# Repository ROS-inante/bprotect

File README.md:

# BProtect

This repository contains the design files and firmware for the BProtect battery management board.

## Overview
The battery management system consists of a LTC4281 Hot-Swap controller handling the power path control as well as a Espressif ESP32 running the interfacing firmware. 

The design was created in KiCad and can be found in the [board](/board) folder.
Some notes about design considerations, component selection and sizing are contained in the schematic.

The ESP32 runs the awesome [Tasmota](https://tasmota.github.io/docs/) firmware and has a custom driver for the LTC4281 written in [Berry](https://berry-lang.github.io/). It can be found in the [app](/app) folder.

## Usage
Assemble the board as per schematics and flash Tasmota (version >=13).
Drop the Berry-script named [ltc4281.be](/app/ltc4281.be) from the [app](/app) folder into the filesystem and add it to the 'autoexec.be' as per the example.

## License
This project is licensed under the GPLv3.

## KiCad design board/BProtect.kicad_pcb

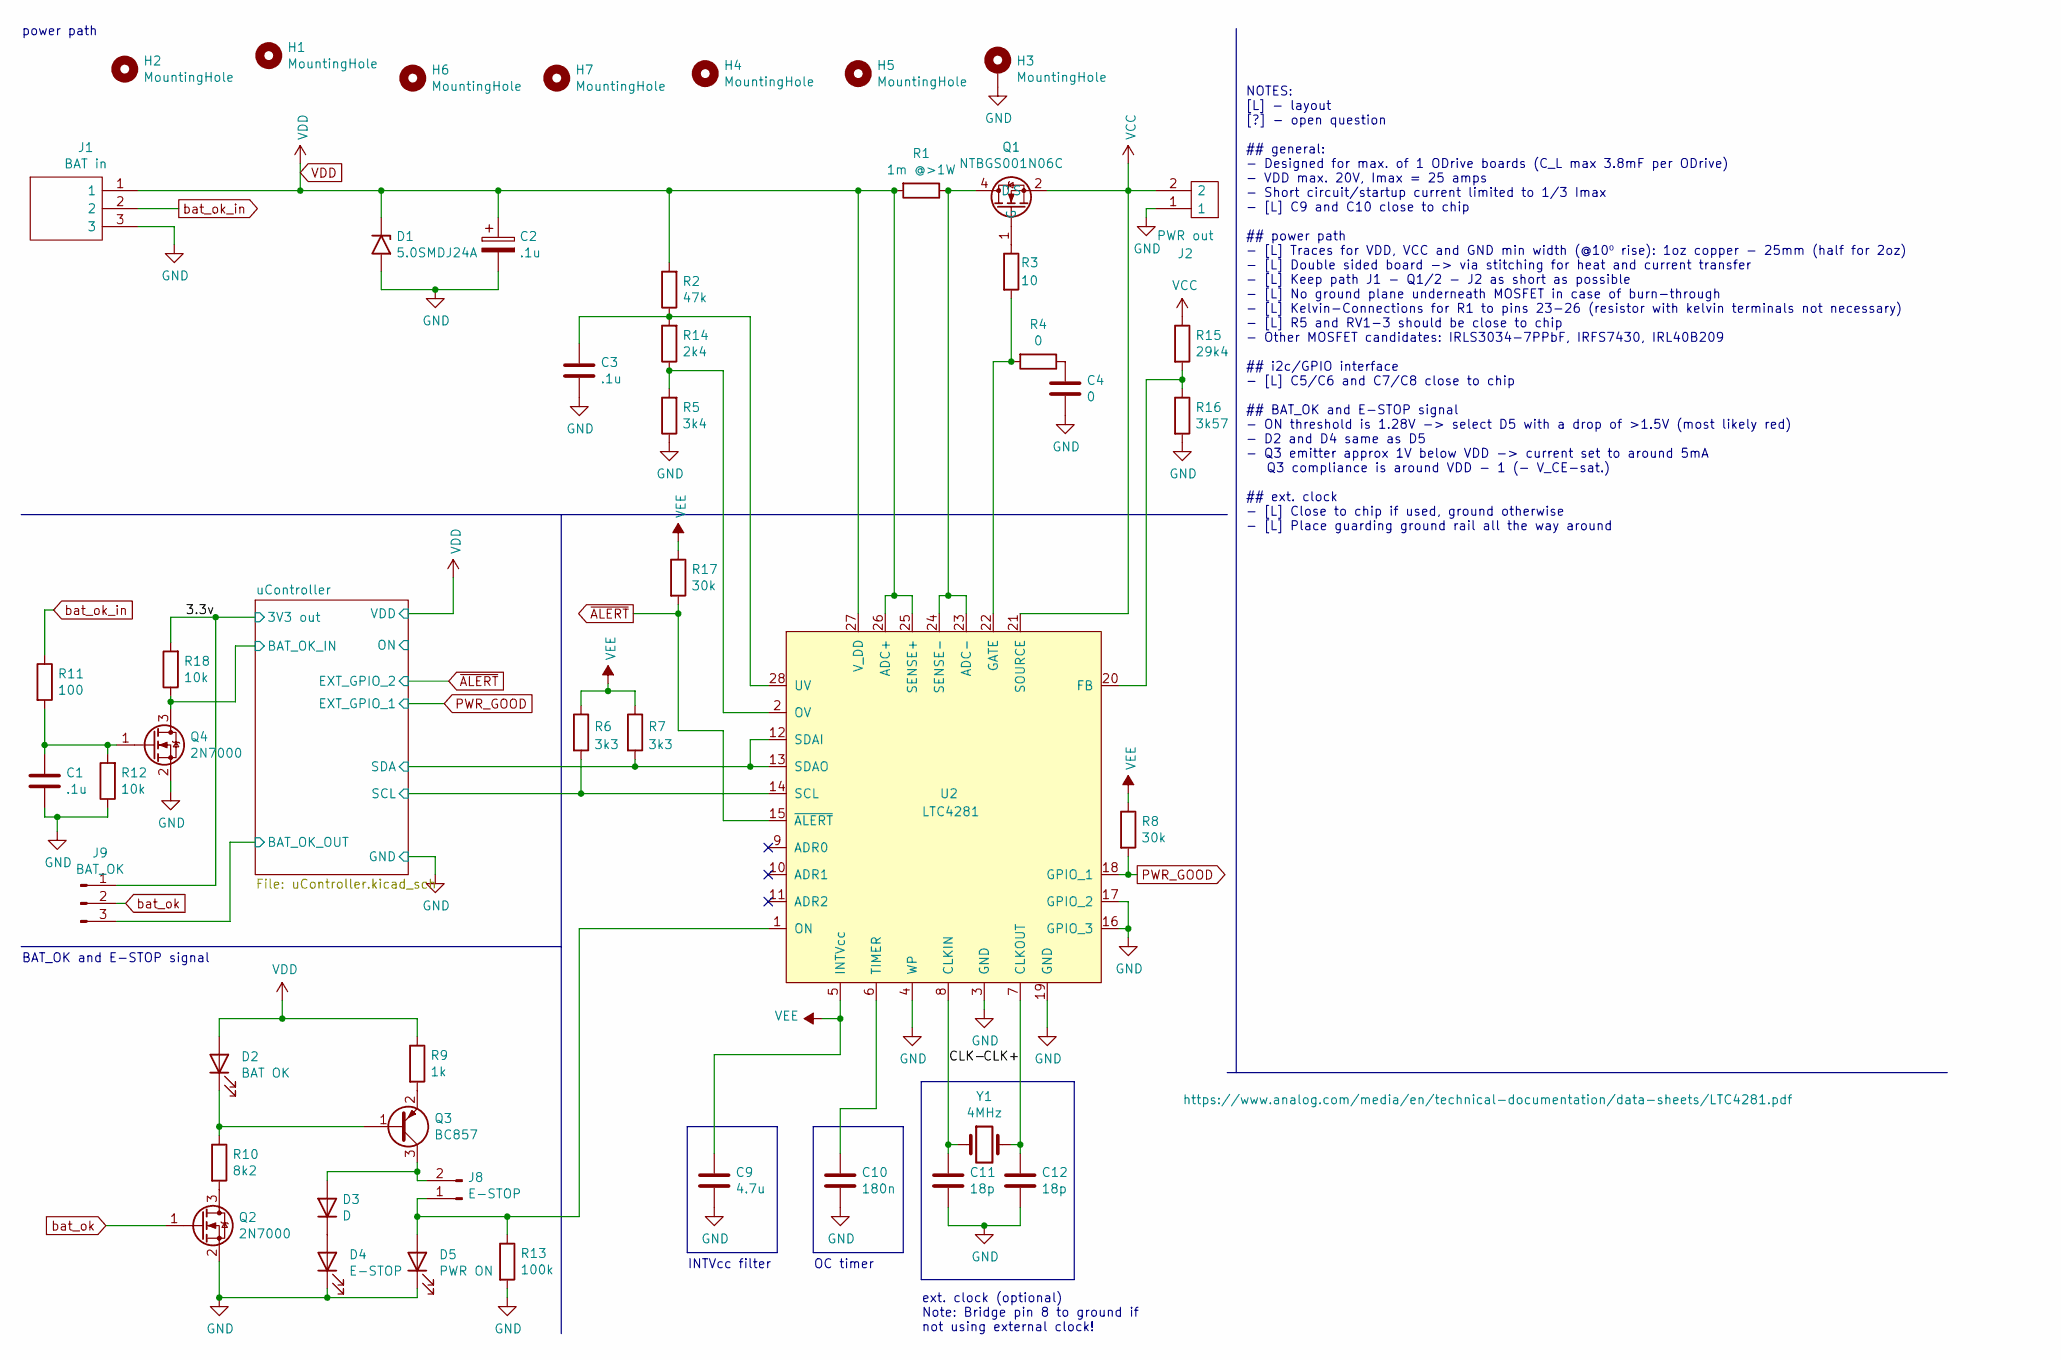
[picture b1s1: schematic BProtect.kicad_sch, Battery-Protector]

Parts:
C1, C3: .1u; C_1206_3216Metric_Pad1.33x1.80mm_HandSolder
C2: .1u; CP_Elec_4x5.4
C4: 0; C_1206_3216Metric_Pad1.33x1.80mm_HandSolder
C9: 4.7u; C_1206_3216Metric_Pad1.33x1.80mm_HandSolder
C10: 180n; C_1206_3216Metric_Pad1.33x1.80mm_HandSolder
C11, C12: 18p; C_0805_2012Metric_Pad1.18x1.45mm_HandSolder
D1: 5.0SMDJ24A; D_SMC_Handsoldering
D2: BAT OK; LED_1206_3216Metric_Pad1.42x1.75mm_HandSolder
D3: D; D_1206_3216Metric_Pad1.42x1.75mm_HandSolder
D4: E-STOP; LED_1206_3216Metric_Pad1.42x1.75mm_HandSolder
D5: PWR ON; LED_1206_3216Metric_Pad1.42x1.75mm_HandSolder
H1, H2, H3, H4, H5, H6, H7: MountingHole; MountingHole_3.2mm_M3_DIN965_Pad_TopBottom
J1: BAT in; 1017522
J2: PWR out; 1017521
J8: E-STOP; conn_SMD_1x03_P2.54mm_Horizontal
J9: BAT_OK; PinHeader_1x03_P2.54mm_Vertical_SMD_Pin1Left
Q1: NTBGS001N06C; TO-263-7_TabPin4
Q2, Q4: 2N7000; TSOT-23
Q3: BC857; TSOT-23
R1: 1m @>1W; R_Shunt_Vishay_WSR2_WSR3_KelvinConnection
R2: 47k; R_1206_3216Metric_Pad1.30x1.75mm_HandSolder
R3: 10; R_1206_3216Metric_Pad1.30x1.75mm_HandSolder
R4: 0; R_1206_3216Metric_Pad1.30x1.75mm_HandSolder
R5: 3k4; R_1206_3216Metric_Pad1.30x1.75mm_HandSolder
R6, R7: 3k3; R_1206_3216Metric_Pad1.30x1.75mm_HandSolder
R8, R17: 30k; R_1206_3216Metric_Pad1.30x1.75mm_HandSolder
R9: 1k; R_1206_3216Metric_Pad1.30x1.75mm_HandSolder
R10: 8k2; R_1206_3216Metric_Pad1.30x1.75mm_HandSolder
R11: 100; R_1206_3216Metric_Pad1.30x1.75mm_HandSolder
R12, R18: 10k; R_1206_3216Metric_Pad1.30x1.75mm_HandSolder
R13: 100k; R_1206_3216Metric_Pad1.30x1.75mm_HandSolder
R14: 2k4; R_1206_3216Metric_Pad1.30x1.75mm_HandSolder
R15: 29k4; R_1206_3216Metric_Pad1.30x1.75mm_HandSolder
R16: 3k57; R_1206_3216Metric_Pad1.30x1.75mm_HandSolder
U2: LTC4281; QFN-28-1EP_4x5mm_P0.5mm_EP2.65x3.65mm
Y1: 4MHz; Crystal_SMD_HC49-SD

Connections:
+3V3: J9.1, R18.2; also elsewhere on the board
/CLK+: C12.1, U2.7 (CLKOUT), Y1.2
/CLK-: C11.1, U2.8 (CLKIN), Y1.1
/uController/BAT_OK_IN: Q4.3 (D), R18.1; also elsewhere on the board
/uController/BAT_OK_OUT: J9.3; also elsewhere on the board
/uController/SCL: R6.2, U2.14 (SCL); also elsewhere on the board
/uController/SDA: R7.2, U2.12 (SDAI), U2.13 (SDAO); also elsewhere on the board
GND: C1.2, C2.2, C3.2, C4.2, C9.2, C10.2, C11.2, C12.2, D1.2 (A2), D4.1 (K), D5.1 (K), H3.1, J1.3, J2.1, Q2.2 (S), Q4.2 (S), R5.1, R12.1, R13.2, R16.2, U2.3 (GND), U2.4 (WP), U2.16 (GPIO_3), U2.17 (GPIO_2), U2.19 (GND), U2.29; also elsewhere on the board
unnamed: C1.1, Q4.1 (G), R11.2, R12.2
unnamed: C3.1, R2.1, R14.2, U2.28 (UV)
unnamed: C4.1, R4.1
unnamed: C10.1, U2.6 (TIMER)
unnamed: D2.1 (K), Q3.1 (B), R10.1
unnamed: D3.1 (K), D4.2 (A)
unnamed: D3.2 (A), J8.2, Q3.3 (C)
unnamed: D5.2 (A), J8.1, R13.1, U2.1 (ON)
unnamed: Q1.1 (G), R3.1
unnamed: Q2.3 (D), R10.2
unnamed: Q3.2 (E), R9.2
unnamed: R3.2, R4.2, U2.22 (GATE)
unnamed: R5.2, R14.1, U2.2 (OV)
unnamed: R15.2, R16.1, U2.20 (FB)
PWR_GOOD: R8.2, U2.18 (GPIO_1); also elsewhere on the board
VDD: C2.1, D1.1 (A1), D2.2 (A), J1.1, R1.2, R2.2, R9.1, U2.25 (SENSE+), U2.26 (ADC+), U2.27 (V_DD); also elsewhere on the board
VEE: C9.1, R6.1, R7.1, R8.1, R17.1, U2.5 (INTVcc)
bat_ok: J9.2, Q2.1 (G)
bat_ok_in: J1.2, R11.1
~ALERT: R17.2, U2.15 (~ALERT); also elsewhere on the board

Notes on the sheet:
INTVcc filter
NOTES: [L] - layout [?] - open question ## general: - Designed for max. of 1 ODrive boards (C_L max 3.8mF per ODrive) - VDD max. 20V, Imax = 25 amps - Short circuit/startup current limited to 1/3 Imax - [L] C9 and C10 close to chip ## power path - [L] Traces for VDD, VCC and GND min width (@10⁰ ris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
power path
BAT_OK and E-STOP signal
OC timer
ext. clock (optional) Note: Bridge pin 8 to ground if not using external clock!

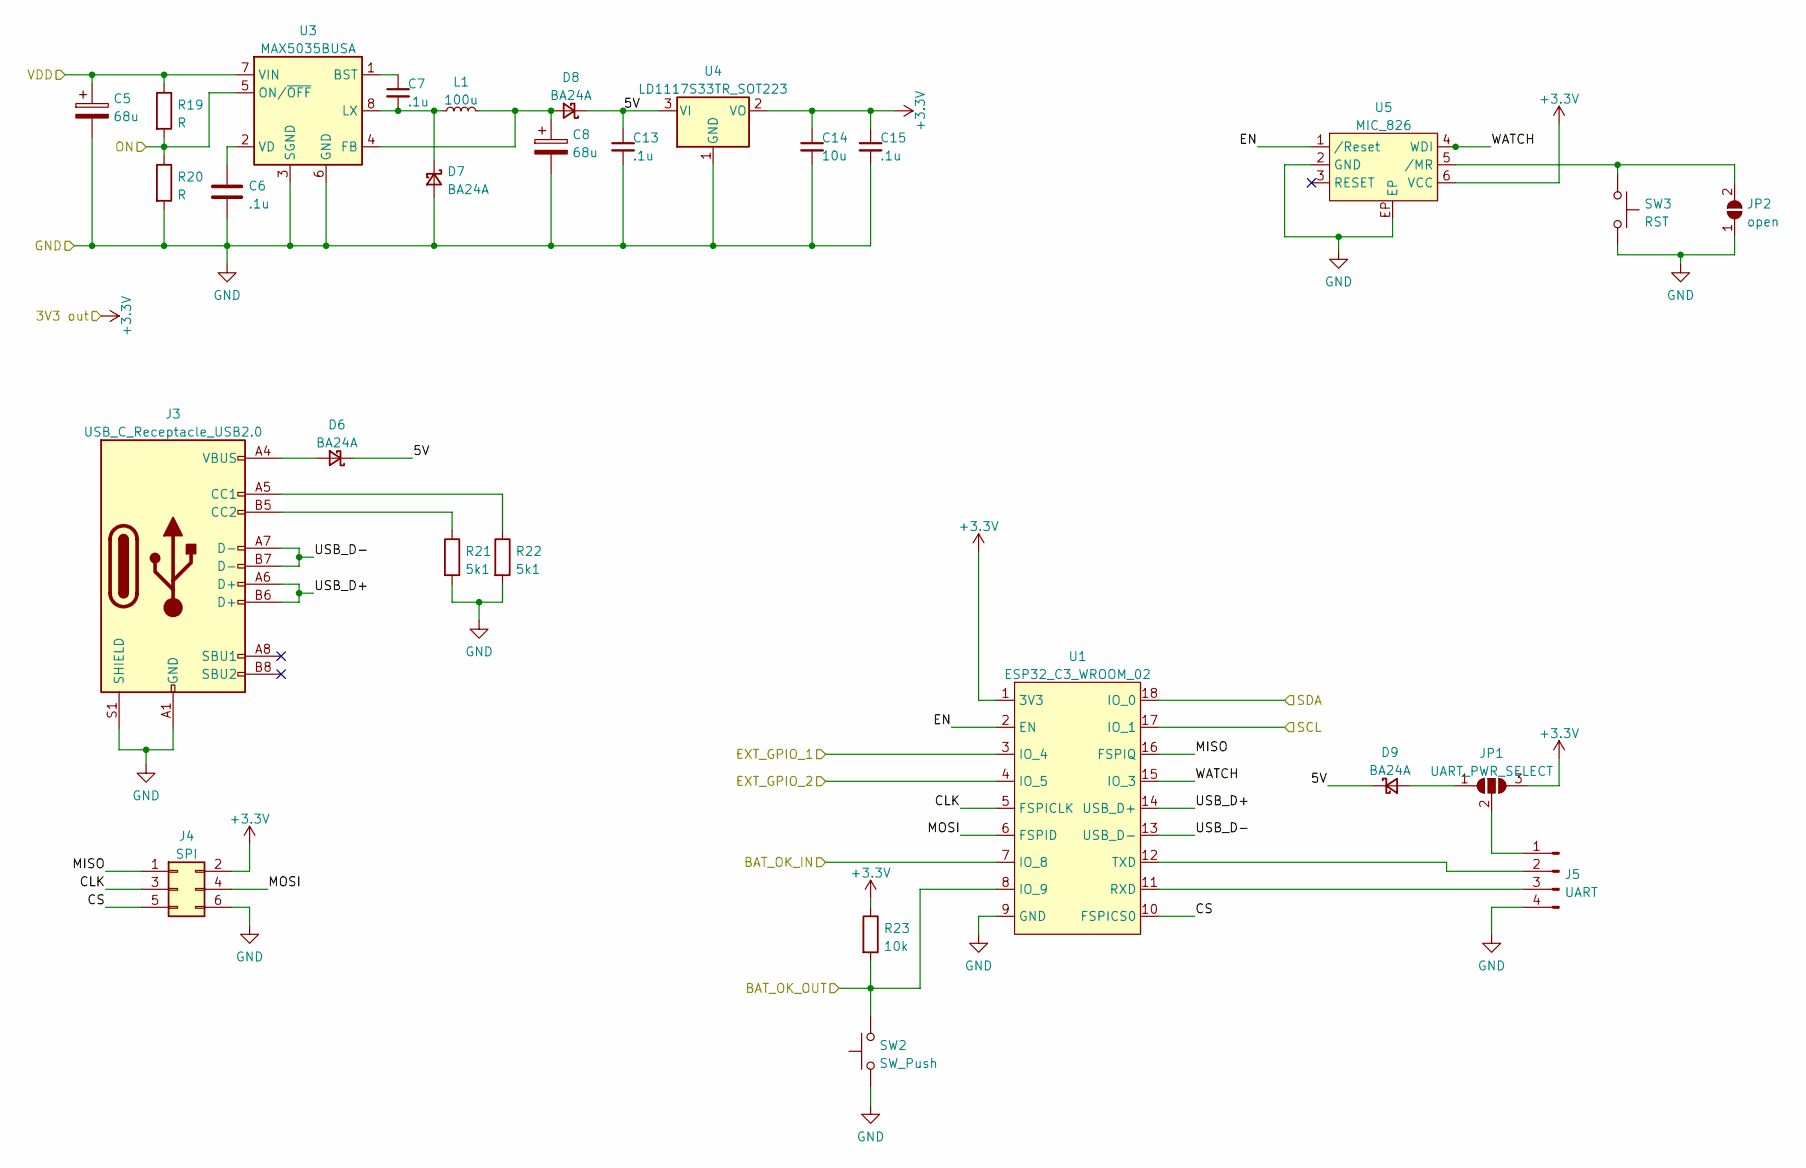
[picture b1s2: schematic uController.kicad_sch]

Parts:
C5, C8: 68u; CP_Elec_4x5.4
C6, C7, C13, C15: .1u; C_1206_3216Metric_Pad1.33x1.80mm_HandSolder
C14: 10u; C_1206_3216Metric_Pad1.33x1.80mm_HandSolder
D6, D7, D8, D9: BA24A; D_SMA
J3: USB_C_Receptacle_USB2.0; USB_C_Receptacle_JAE_DX07S016JA1R1500
J4: SPI; PinSocket_2x03_P2.54mm_Vertical
J5: UART; PinSocket_1x04_P2.54mm_Vertical
JP1: UART_PWR_SELECT; SolderJumper-3_P1.3mm_Open_RoundedPad1.0x1.5mm_NumberLabels
JP2: open; SolderJumper-2_P1.3mm_Open_RoundedPad1.0x1.5mm
L1: 100u; L_12x12mm_H8mm
R19, R20: R; R_1206_3216Metric_Pad1.30x1.75mm_HandSolder
R21, R22: 5k1; R_1206_3216Metric_Pad1.30x1.75mm_HandSolder
R23: 10k; R_1206_3216Metric_Pad1.30x1.75mm_HandSolder
SW2: SW_Push; SW_Push_1P1T_NO_CK_KSC2xxJ
SW3: RST; SW_Push_1P1T_NO_CK_KSC2xxJ
U1: ESP32_C3_WROOM_02; ESP-13-WROOM-02
U3: MAX5035BUSA; SOIC-8_3.9x4.9mm_P1.27mm
U4: LD1117S33TR_SOT223; SOT-223-3_TabPin2
U5: MIC_826; TDFN-6-1EP_1.6x1.6mm_P0.5mm_EP0.5x1.4mm

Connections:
+3V3: C14.1, C15.1, J4.2, JP1.3 (B), R23.1, U1.1 (3V3), U4.2 (VO), U5.6 (VCC); also elsewhere on the board
/uController/5V: C13.1, D6.1 (K), D8.1 (K), D9.1 (K), U4.3 (VI)
/uController/BAT_OK_IN: U1.7 (IO_8); also elsewhere on the board
/uController/BAT_OK_OUT: R23.2, SW2.2, U1.8 (IO_9); also elsewhere on the board
/uController/CLK: J4.3, U1.5 (FSPICLK)
/uController/CS: J4.5, U1.10 (FSPICS0)
/uController/EN: U1.2 (EN), U5.1 (/Reset)
/uController/MISO: J4.1, U1.16 (FSPIQ)
/uController/MOSI: J4.4, U1.6 (FSPID)
/uController/ON: R19.2, R20.1, U3.5 (ON/~OFF)
/uController/SCL: U1.17 (IO_1); also elsewhere on the board
/uController/SDA: U1.18 (IO_0); also elsewhere on the board
/uController/USB_D+: J3.A6 (D+), J3.B6 (D+), U1.14 (USB_D+)
/uController/USB_D-: J3.A7 (D-), J3.B7 (D-), U1.13 (USB_D-)
/uController/WATCH: U1.15 (IO_3), U5.4 (WDI)
GND: C5.2, C6.2, C8.2, C13.2, C14.2, C15.2, D7.2 (A), J3.A1 (GND), J3.A12 (GND), J3.B1 (GND), J3.B12 (GND), J3.S1 (SHIELD), J4.6, J5.4, JP2.1 (A), R20.2, R21.2, R22.2, SW2.1, SW3.2, U1.9 (GND), U1.PAD, U3.3 (SGND), U3.6 (GND), U4.1 (GND), U5.2 (GND), U5.EP; also elsewhere on the board
unnamed: C6.1, U3.2 (VD)
unnamed: C7.1, U3.1 (BST)
unnamed: C7.2, D7.1 (K), L1.1, U3.8 (LX)
unnamed: C8.1, D8.2 (A), L1.2, U3.4 (FB)
unnamed: D6.2 (A), J3.A4 (VBUS), J3.A9 (VBUS), J3.B4 (VBUS), J3.B9 (VBUS)
unnamed: D9.2 (A), JP1.1 (A)
unnamed: J3.A5 (CC1), R22.1
unnamed: J3.B5 (CC2), R21.1
unnamed: J5.1, JP1.2 (C)
unnamed: J5.2, U1.12 (TXD)
unnamed: J5.3, U1.11 (RXD)
unnamed: JP2.2 (B), SW3.1, U5.5 (/MR)
PWR_GOOD: U1.3 (IO_4); also elsewhere on the board
VDD: C5.1, R19.1, U3.7 (VIN); also elsewhere on the board
~ALERT: U1.4 (IO_5); also elsewhere on the board

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
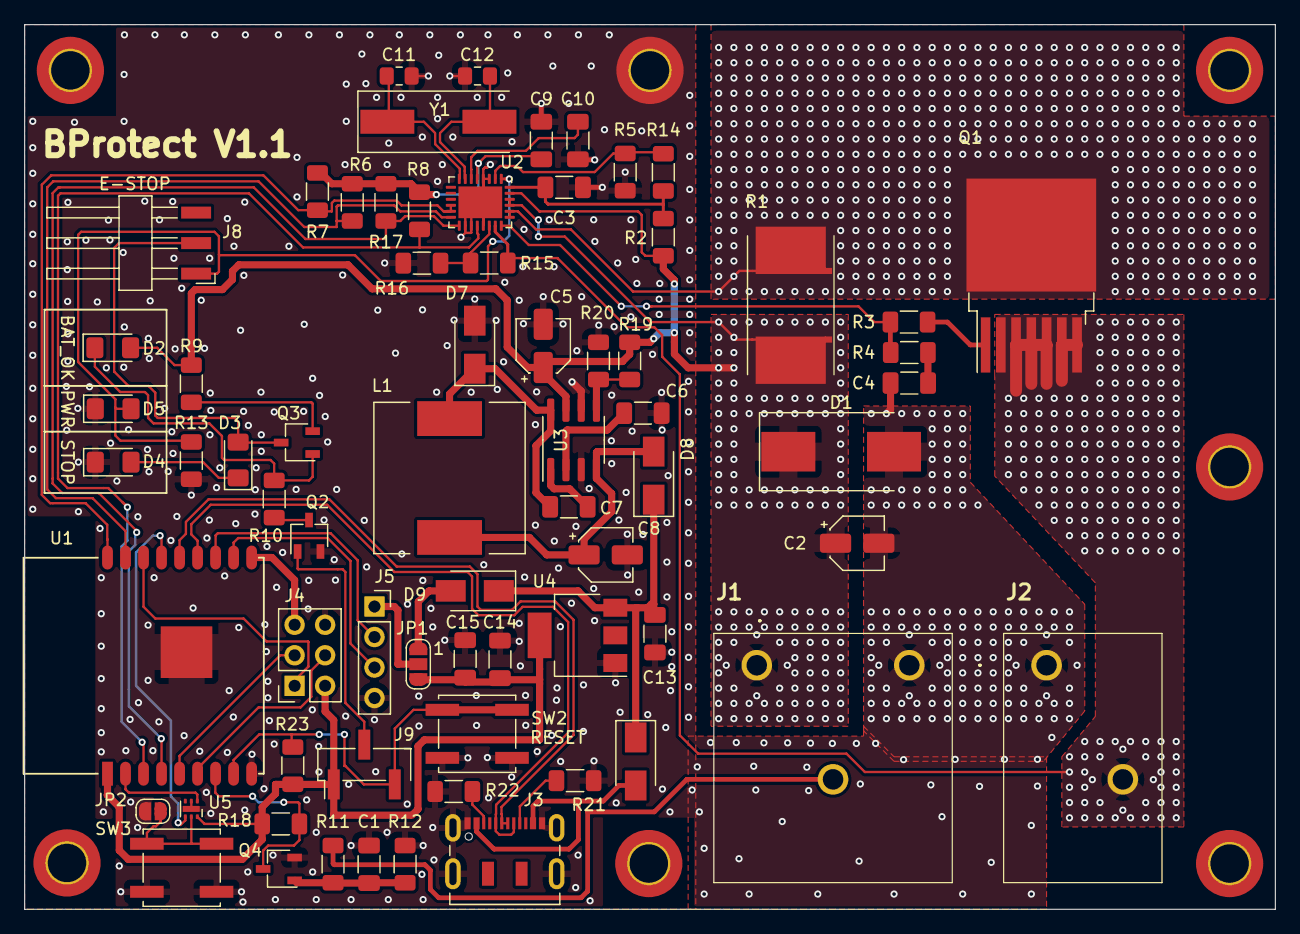
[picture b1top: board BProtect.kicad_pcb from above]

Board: 2 copper layers, 104.1 x 73.7 mm, 76 parts (0 on the bottom side), 52 nets.

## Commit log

2024-01-24 Added license.
2024-01-24 Added README
2024-01-24 Added board design files.
2024-01-25 Added berry driver
